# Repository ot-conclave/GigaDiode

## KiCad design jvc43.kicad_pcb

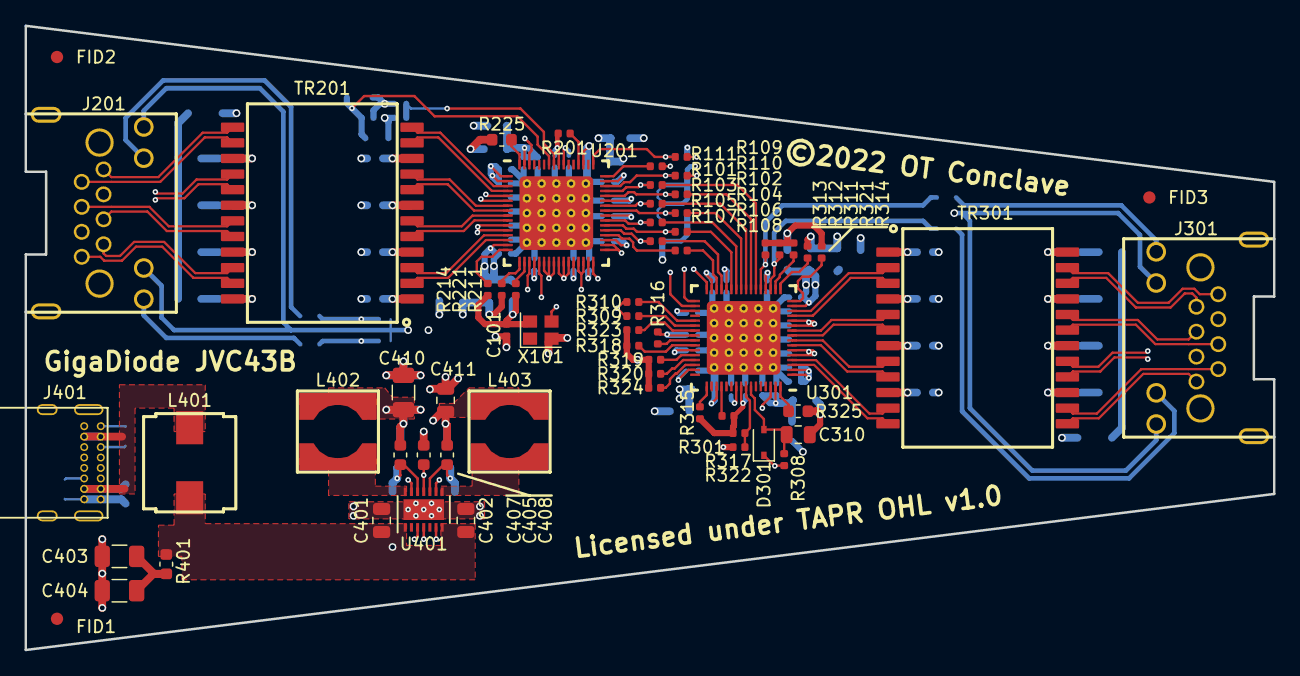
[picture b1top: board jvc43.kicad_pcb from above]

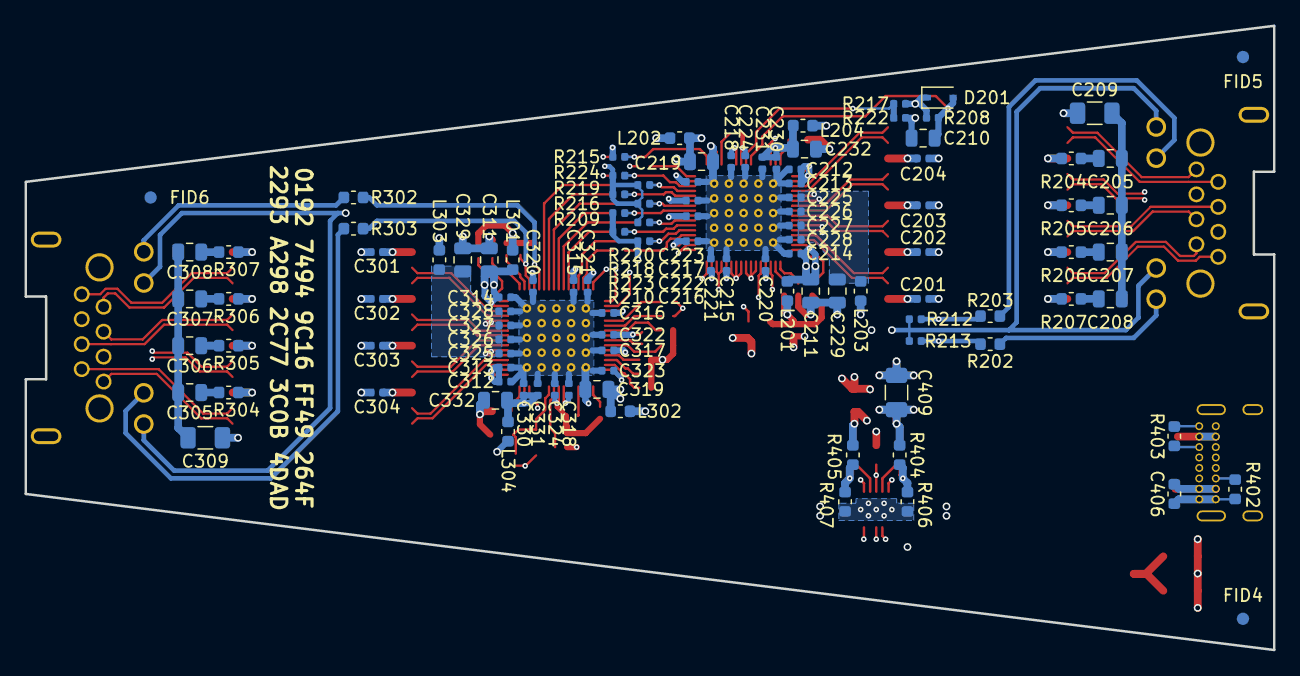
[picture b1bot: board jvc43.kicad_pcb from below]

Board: 6 copper layers, 101.6 x 50.8 mm, 172 parts (109 on the bottom side), 135 nets.

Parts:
C101, C201, C202, C203, C204, C212, C213, C214, C215, C216, C217, C218, C220, C221, C222, C223, C224, C225, C226, C227, C228, C231, C301, C302, C303, C304, C312, C313, C314, C315, C316, C317, C318, C320, C321, C322, C323, C324, C325, C326, C327, C328, C331: 0.1u; C_0402_1005Metric
C205, C206, C207, C208, C305, C306, C307, C308: 22n; C_0805_2012Metric
C209, C309: 1n; C_1206_3216Metric
C210, C211, C219, C229, C310, C311, C319, C329: 10u; C_0805_2012Metric
C230, C330: 10n; C_0402_1005Metric
C232, C332, C401, C402, C411: 4.7u; C_0805_2012Metric
C403, C404, C409, C410: 22u; C_1206_3216Metric
C405, C406: 1u; C_0603_1608Metric
C407, C408: 22p; C_0603_1608Metric
D201, D301: 1N4148WS; D_SOD-323
FID1, FID2, FID3, FID4, FID5, FID6: Fiducial_1mm_Dia_2mm_Outer
J201, J301: 8P8C_LED_Shielded; RJ45_Amphenol_RJE73-188-00XX1-0X
J401: USB_C_Receptacle_USB2.0; USB_C_GCT_USB4085
L201, L202, L203, L204, L301, L302, L303, L304: 470 ohm; L_0603_1608Metric
L401: 47uH; L_Panasonic_ETQ-P4MxxxKFM
L402: 6.2uH; L_5.8x5.8mm_cutcir_6.3mm
L403: 15uH; L_5.8x5.8mm_cutcir_6.3mm
R101, R102, R103, R104, R105, R106, R107, R108, R109, R110, R111: 22; R_0402_1005Metric
R201, R208, R209, R210, R211, R212, R213, R214, R215, R216, R301, R308, R309, R310, R311, R312, R313, R314, R315, R316: 10k; R_0402_1005Metric
R202, R203, R302, R303: 220; R_0603_1608Metric
R204, R205, R206, R207, R304, R305, R306, R307: 75; R_0603_1608Metric
R217, R317: dnp; R_0402_1005Metric
R218, R219, R220, R221, R222, R223, R224, R318, R319, R320, R321, R322, R323, R324: 1k; R_0402_1005Metric
R225, R325: 6.04k; R_0603_1608Metric
R401: 2.1; R_0603_1608Metric
R402, R403: 5.1k; R_0603_1608Metric
R404: 84.5k; R_0603_1608Metric
R405: 316k; R_0603_1608Metric
R406, R407: 100k; R_0603_1608Metric
TR201, TR301: PT61020EL; magnetics_PT61020E
U201, U301: LAN8831; QFN-64-1EP_8x8mm_P0.4mm_EP6x6mm_ThermalVias
U401: LTC3622*DE; DFN-14-1EP_3x4mm_P0.5mm_EP1.7x3.3mm
X101: 25 MHz; Crystal_SMD_2520-4Pin_2.5x2.0mm

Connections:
+1V1: C407.1, C409.1, C410.1, L202.2, L203.2, L204.2, L302.2, L303.2, L304.2, L402.1, R404.1
+2V5: C101.1, C220.1, C221.1, C222.1, C223.1, C224.1, C320.1, C321.1, C322.1, C323.1, C324.1, C408.1, C411.1, D201.1, D301.1, J201.9, J201.11, J301.9, J301.11, L201.1, L301.1, L403.2, R201.2, R208.1, R209.1, R210.1, R211.1, R212.1, R213.1, R214.1, R215.1, R216.1, R217.1, R301.2, R308.1, R309.1, R310.1, R311.1, R312.1, R313.1, R314.1, R315.1, R316.1, R317.1, R405.1, U201.20, U201.31, U201.40, U201.47, U201.56, U301.20, U301.31, U301.40, U301.47, U301.56, X101.4
/CLK_W2B: R109.1, U301.33
/EN_W2B: R110.1, U301.34
/ER_W2B: R111.1, U301.32
/Ethernet1/CLK125: R217.2, R222.1, U201.57
/Ethernet1/ETH_CR0: C204.1, TR201.10
/Ethernet1/ETH_CR1: C203.1, TR201.7
/Ethernet1/ETH_CR2: C202.1, TR201.4
/Ethernet1/ETH_CR3: C201.1, TR201.1
/Ethernet1/ETH_CT0: R204.1, TR201.15
/Ethernet1/ETH_CT1: R205.1, TR201.18
/Ethernet1/ETH_CT2: R206.1, TR201.21
/Ethernet1/ETH_CT3: R207.1, TR201.24
/Ethernet1/ETH_TR0+: TR201.12, U201.3
/Ethernet1/ETH_TR0-: TR201.11, U201.4
/Ethernet1/ETH_TR1+: TR201.9, U201.7
/Ethernet1/ETH_TR1-: TR201.8, U201.8
/Ethernet1/ETH_TR2+: TR201.6, U201.9
/Ethernet1/ETH_TR2-: TR201.5, U201.10
/Ethernet1/ETH_TR3+: TR201.3, U201.13
/Ethernet1/ETH_TR3-: TR201.2, U201.14
/Ethernet1/ETH_TX0+: J201.1, TR201.13
/Ethernet1/ETH_TX0-: J201.2, TR201.14
/Ethernet1/ETH_TX1+: J201.3, TR201.16
/Ethernet1/ETH_TX1-: J201.6, TR201.17
/Ethernet1/ETH_TX2+: J201.4, TR201.19
/Ethernet1/ETH_TX2-: J201.5, TR201.20
/Ethernet1/ETH_TX3+: J201.7, TR201.22
/Ethernet1/ETH_TX3-: J201.8, TR201.23
/Ethernet1/ISET: R225.1, U201.64
/Ethernet1/LED1: R202.1, R213.2, U201.21
/Ethernet1/LED2: R203.1, R212.2, U201.19
/Ethernet1/LED3: R211.2, U201.18
/Ethernet1/LED4: R221.1, U201.17
/Ethernet1/LED5: R214.2, U201.16
/Ethernet1/MDIO: R201.1, U201.52
/Ethernet1/RXCLK: R109.2, R215.2, U201.49
/Ethernet1/RXDV: R110.2, R224.1, U201.46
/Ethernet1/RXER: R111.2, U201.48
/Ethernet1/VDD: C215.1, C216.1, C217.1, C218.1, C219.1, L202.1, U201.28, U201.35, U201.43, U201.55
/Ethernet1/VDDAH: C211.1, C212.1, C213.1, C214.1, L201.2, U201.1, U201.2, U201.15
/Ethernet1/VDDAL: C225.1, C226.1, C227.1, C228.1, C229.1, L203.1, U201.5, U201.6, U201.11, U201.12
/Ethernet1/VDDAL_PLL: C230.1, C231.1, C232.1, L204.1, U201.63
/Ethernet1/XI: U201.62, U301.62, X101.3
/Ethernet1/eth_inter_gnd: C205.2, C206.2, C207.2, C208.2, C209.1
/Ethernet1/gnd_eth: C209.2, J201.SH
/Ethernet1/green: J201.10, R203.2
/Ethernet1/nRST: C210.1, D201.2, R208.2, U201.58
/Ethernet1/yellow: J201.12, R202.2
/Ethernet2/CLK125: R317.2, R322.1, U301.57
/Ethernet2/ETH_CR0: C304.1, TR301.10
/Ethernet2/ETH_CR1: C303.1, TR301.7
/Ethernet2/ETH_CR2: C302.1, TR301.4
/Ethernet2/ETH_CR3: C301.1, TR301.1
/Ethernet2/ETH_CT0: R304.1, TR301.15
/Ethernet2/ETH_CT1: R305.1, TR301.18
/Ethernet2/ETH_CT2: R306.1, TR301.21
/Ethernet2/ETH_CT3: R307.1, TR301.24
/Ethernet2/ETH_TR0+: TR301.12, U301.3
/Ethernet2/ETH_TR0-: TR301.11, U301.4
/Ethernet2/ETH_TR1+: TR301.9, U301.7
/Ethernet2/ETH_TR1-: TR301.8, U301.8
/Ethernet2/ETH_TR2+: TR301.6, U301.9
/Ethernet2/ETH_TR2-: TR301.5, U301.10
/Ethernet2/ETH_TR3+: TR301.3, U301.13
/Ethernet2/ETH_TR3-: TR301.2, U301.14
/Ethernet2/ETH_TX0+: J301.1, TR301.13
/Ethernet2/ETH_TX0-: J301.2, TR301.14
/Ethernet2/ETH_TX1+: J301.3, TR301.16
/Ethernet2/ETH_TX1-: J301.6, TR301.17
/Ethernet2/ETH_TX2+: J301.4, TR301.19
/Ethernet2/ETH_TX2-: J301.5, TR301.20
/Ethernet2/ETH_TX3+: J301.7, TR301.22
/Ethernet2/ETH_TX3-: J301.8, TR301.23
/Ethernet2/ISET: R325.1, U301.64
/Ethernet2/LED1: R302.1, R313.2, U301.21
/Ethernet2/LED2: R303.1, R312.2, U301.19
/Ethernet2/LED3: R311.2, U301.18
/Ethernet2/LED4: R321.1, U301.17
/Ethernet2/LED5: R314.2, U301.16
/Ethernet2/MDIO: R301.1, U301.52
/Ethernet2/RXCLK: R315.2, U301.49
/Ethernet2/RXD0: R320.1, U301.45
/Ethernet2/RXD1: R319.1, U301.44
/Ethernet2/RXD2: R318.1, U301.42
/Ethernet2/RXD3: R316.2, U301.41
/Ethernet2/RXD4: R323.1, U301.39
/Ethernet2/RXD5: R309.2, U301.38
/Ethernet2/RXD6: R310.2, U301.37
/Ethernet2/RXDV: R324.1, U301.46
/Ethernet2/VDD: C315.1, C316.1, C317.1, C318.1, C319.1, L302.1, U301.28, U301.35, U301.43, U301.55
/Ethernet2/VDDAH: C311.1, C312.1, C313.1, C314.1, L301.2, U301.1, U301.2, U301.15
/Ethernet2/VDDAL: C325.1, C326.1, C327.1, C328.1, C329.1, L303.1, U301.5, U301.6, U301.11, U301.12
/Ethernet2/VDDAL_PLL: C330.1, C331.1, C332.1, L304.1, U301.63
/Ethernet2/eth_inter_gnd: C305.2, C306.2, C307.2, C308.2, C309.1
/Ethernet2/gnd_eth: C309.2, J301.SH
/Ethernet2/green: J301.10, R303.2
/Ethernet2/nRST: C310.1, D301.2, R308.2, U301.58
/Ethernet2/yellow: J301.12, R302.2
/Power_Supply/CC1: J401.A5, R403.1
/Power_Supply/CC2: J401.B5, R402.1
/Power_Supply/FB1: C407.2, R404.2, R406.1, U401.12
/Power_Supply/FB2: C408.2, R405.2, R407.1, U401.10
/Power_Supply/IntVcc: C405.1, U401.4, U401.11
/Power_Supply/PS_Vin: C401.1, C402.1, L401.2, R401.1, U401.1, U401.7, U401.9, U401.13
/Power_Supply/SW1: L402.2, U401.14
/Power_Supply/SW2: L403.1, U401.8
/Power_Supply/VCC_USB: C406.1, J401.A4, J401.A9, J401.B4, J401.B9, L401.1
/Power_Supply/Vin_damp: C403.1, C404.1, R401.2
/RXD0: R101.2, R220.1, U201.45
/RXD1: R102.2, R219.1, U201.44
/RXD2: R103.2, R218.1, U201.42
/RXD3: R104.2, R216.2, U201.41
/RXD4: R105.2, R223.1, U201.39
/RXD5: R106.2, R209.2, U201.38
/RXD6: R107.2, R210.2, U201.37
/RXD7: R108.2, U201.36
/TXD0: R101.1, U301.22
/TXD1: R102.1, U301.23
/TXD2: R103.1, U301.24
/TXD3: R104.1, U301.25
/TXD4: R105.1, U301.26
/TXD5: R106.1, U301.27
/TXD6: R107.1, U301.29
/TXD7: R108.1, U301.30
GND: C101.2, C201.2, C202.2, C203.2, C204.2, C210.2, C211.2, C212.2, C213.2, C214.2, C215.2, C216.2, C217.2, C218.2, C219.2, C220.2, C221.2, C222.2, C223.2, C224.2, C225.2, C226.2, C227.2, C228.2, C229.2, C230.2, C231.2, C232.2, C301.2, C302.2, C303.2, C304.2, C310.2, C311.2, C312.2, C313.2, C314.2, C315.2, C316.2, C317.2, C318.2, C319.2, C320.2, C321.2, C322.2, C323.2, C324.2, C325.2, C326.2, C327.2, C328.2, C329.2, C330.2, C331.2, C332.2, C401.2, C402.2, C403.2, C404.2, C405.2, C406.2, C409.2, C410.2, C411.2, J401.A1, J401.A12, J401.B1, J401.B12, J401.S1, R218.2, R219.2, R220.2, R221.2, R222.2, R223.2, R224.2, R225.2, R318.2, R319.2, R320.2, R321.2, R322.2, R323.2, R324.2, R325.2, R402.2, R403.2, R406.2, R407.2, U201.22, U201.23, U201.24, U201.25, U201.26, U201.27, U201.29, U201.30, U201.32, U201.33, U201.34, U201.51, U201.PAD, U301.51, U301.PAD, U401.3, U401.6, U401.15, X101.2
unnamed: C205.1, R204.2
unnamed: C206.1, R205.2
unnamed: C207.1, R206.2
unnamed: C208.1, R207.2
unnamed: C305.1, R304.2
unnamed: C306.1, R305.2
unnamed: C307.1, R306.2
unnamed: C308.1, R307.2

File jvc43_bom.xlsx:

Reference | Qty | Value | Footprint | Datasheet | Part# | Voltage | Tolerance | Isat
C101 C201 C202 C203 C204 C212 C213 C214 C215 C216 C217 C218 C220 C221 C222 C223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 | 43 | 0.1u | Capacitor_SMD:C_0402_1005Metric | ~ | CGA2B1X7R1C104K050BC | 16V
C205 C206 C207 C208 C305 C306 C307 C308 | 8 | 22n | Capacitor_SMD:C_0805_2012Metric | ~ | CGA4J3X7R2E223K125AA | 250V
C209 C309 | 2 | 1n | Capacitor_SMD:C_1206_3216Metric | ~ | C1206X102KGRACAUTO | 2kV
C210 C211 C310 C311 | 4 | 10u | Capacitor_SMD:C_0805_2012Metric | ~ | GCM21BR71A106KE22L | 10V
C219 C229 C319 C329 | 4 | 10u | Capacitor_SMD:C_0805_2012Metric | ~ | CGA4J1X7R0J106K125AC | 6.3V
C230 C330 | 2 | 10n | Capacitor_SMD:C_0402_1005Metric | ~ | CGA2B2X7R1E103K050BA | 6.3V
C232 C332 | 2 | 4.7u | Capacitor_SMD:C_0805_2012Metric | ~ | CGA4J3X7R1C475M125AB | 6.3V
C401 C402 | 2 | 4.7u | Capacitor_SMD:C_0805_2012Metric | ~ | CGA4J3X7R1C475M125AB | 16V
C403 C404 | 2 | 22u | Capacitor_SMD:C_1206_3216Metric | ~ | GCJ31CR71A226KE01K | 10V
C405 | 1 | 1u | Capacitor_SMD:C_0603_1608Metric | ~ | CGA3E1X7R1E105K080AC | 10V
C406 | 1 | 1u | Capacitor_SMD:C_0603_1608Metric | ~ | CGA3E1X7R1E105K080AC | 25V
C407 C408 | 2 | 22p | Capacitor_SMD:C_0603_1608Metric | ~ | CGA3E2NP01H220J080AA
C409 C410 | 2 | 22u | Capacitor_SMD:C_1206_3216Metric | ~ | CGA5L1X7R0J226M160AC | 6.3V
C411 | 1 | 4.7u | Capacitor_SMD:C_0805_2012Metric | ~ | CGA4J3X7R1C475M125AB | 10V
D201 D301 | 2 | 1N4148WS | Diode_SMD:D_SOD-323 | ~ | 1N4148WS-E3-08
J201 J301 | 2 | 8P8C_LED_Shielded | myfp:RJ45_Amphenol_RJE73-188-00XX1-0X | ~ | RJE73-188-00440
J401 | 1 | USB_C_Receptacle_USB2.0 | myfp:USB_C_GCT_USB4085 | https://www.usb.org/sites/default/files/documents/usb_type-c.zip | USB4085-GF-A
L201 L202 L203 L204 L301 L302 L303 L304 | 8 | 470 ohm | Inductor_SMD:L_0603_1608Metric | ~ | MPZ1608S601ATD25
L401 | 1 | 47uH | myfp:L_Panasonic_ETQ-P4MxxxKFM | ~ | ETQ-P4M470KFM |  |  | >3.0A
L402 | 1 | 6.2uH | myfp:L_5.8x5.8mm_cutcir_6.3mm | ~ | SRR5028-6R2Y
L403 | 1 | 15uH | myfp:L_5.8x5.8mm_cutcir_6.3mm | ~ | SRR5028-150Y
R101 R102 R103 R104 R105 R106 R107 R108 R109 R110 R111 | 11 | 22 | Resistor_SMD:R_0402_1005Metric | ~ | ERJ-2RKF22R0X
R201 R208 R209 R210 R211 R212 R213 R214 R215 R216 R218 R219 R220 R221 R222 R223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 | 34 | 10k | Resistor_SMD:R_0402_1005Metric | ~ | ERJ-2RKF1002X
R202 R203 R302 R303 | 4 | 220 | Resistor_SMD:R_0603_1608Metric | ~ | ERJ-3EKF1000V
R204 R205 R206 R207 R304 R305 R306 R307 | 8 | 75 | Resistor_SMD:R_0603_1608Metric | ~ | ERJ-3EKF75R0V
R217 R317 | 2 | dnp | Resistor_SMD:R_0402_1005Metric | ~ | dnp
R225 R325 | 2 | 6.04k | Resistor_SMD:R_0603_1608Metric | ~ | ERJ-3EKF6041V
R401 | 1 | 2.1000000000000001 | Resistor_SMD:R_0603_1608Metric | ~ | ERJ-3GEYJ2R2V
R402 R403 | 2 | 5.1k | Resistor_SMD:R_0603_1608Metric | ~ | ERJ-3EKF5101V
R404 | 1 | 84.5k | Resistor_SMD:R_0603_1608Metric | ~ | ERJ-3EKF8452V |  | 0.01
R405 | 1 | 316k | Resistor_SMD:R_0603_1608Metric | ~ | ERJ-3EKF3163V |  | 0.01
R406 R407 | 2 | 100k | Resistor_SMD:R_0603_1608Metric | ~ | ERJ-3EKF1003V |  | 0.01
TR201 TR301 | 2 | PT61020EL | myfp:magnetics_PT61020E |  | PT61020EL
U201 U301 | 2 | LAN8831 | myfp:QFN-64-1EP_8x8mm_P0.4mm_EP6x6mm_ThermalVias |  | LAN8831-V/Q2A
U401 | 1 | LTC3622*DE | Package_DFN_QFN:DFN-14-1EP_3x4mm_P0.5mm_EP1.7x3.3mm |  | LTC3622IDE#PBF
X101 | 1 | 25 MHz | Crystal:Crystal_SMD_2520-4Pin_2.5x2.0mm | ~ | ECS-2520MV-250-CN-TR

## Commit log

2022-12-05 New project
2022-12-05 Created schematic symbol for LAN8810 chip.
2022-12-05 - Created QFN72 footprint for LAN8810 chip - Started basic schematic power bypassing - Imported into layout to get an initial look
2022-12-06 - Picked a GigE transformer - Created schematic symbol & footprint for it - Added to design with bare hookup to PHY
2022-12-06 - Selected a shielded RJ45 with dual LEDs, with the cable orientation such that it makes the transformer-to-RJ45 wiring nice. - Added a second whole Ethernet port and connected the two ports together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
2022-12-06 - Added termination network to line side of Ethernet transformer - Started vaguely laying out the big pieces of Ethernet1 block - Set PCB layout to be six layers - Added layout layer identification t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
2022-12-06 - Adjusted RJ45 main pin thru-holes to have only an 8mil-wide ring, instead of 10mil. There was just not enough room for routing. - Fixed wiring to RJ45, it was 3/4 and 5/6 instead of 3/6 and 4/5, wh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
2022-12-07 Lots of work. - Bussed the two Ethernet blocks together in top level schematic - Mashed Ethernet1 input wires to ground - Added hierarchical label for crystal-in pin - Added a couple more net labels 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
2022-12-08 - Added copyright and license headers to the schematic - Started in on the power supply, from 0 to 80% or so, including documentation
2022-12-08 Added license/copyright to layout file.
2022-12-08 Added the text of the TAPR OHL v1.0
2022-12-08 Experimenting with plotting options. "Plot sheet reference on all layers" ensures that the licensing text is included in all Gerber output files. The board houses might get annoyed, will have to see.
2022-12-08 Major work on the power supply: - Swapped the input filter inductor for a significantly smaller one - Basically finished laying out the switching supply
2022-12-08 Forward progress - Started the real 1.2V power plane - Placed and routed most of PHY1 decoupling capacitors - Placed and partly routed transformer2 PHY-side resistors & capacitors - Labelled a few mo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
2022-12-08 Routed Ethernet2 RJ45-to-transformer area.
2022-12-08 Routed 3/4 of the PHY2 decoupling caps, plus the PHY1-to-PHY2 data lines (but not yet the enables/clock). Had to alter some traces and clearances down from 8 mils to 7 mils to get a couple things to 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
2022-12-09 - Routed the PHY2-to-magnetics diff pairs - Routed all the remaining PHY2 decoupling caps, and even the chip inductors, except for the VDD_ETH one - Spent some time swizzling rear silkscreen labels t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
2022-12-09 Placed and routed the tricky last 1/4 of bypass caps for PHY1.
2022-12-09 - Selected, schematic'd, placed & routed a crystal oscillator - Filled various internal planes to even out board thickness as well as improve EMI performance - Added some identifying text to the top 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
2022-12-09 - Removed C201/C301 which were the first two bypass caps on VCC_ETH - Placed last two components - Tweaked some planes, I think? - Finished routing all nets from the current schematic!!!
2022-12-09 - Added HPD_MODE strap resistor - Narrowed down from an RJ45 family P/N to a very specific P/N - Added RJ45 LED hookups - Added CONFIG0/1/2/3 hookups, including a bunch of 0402 zero-ohm options - Pla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
2022-12-09 Added an identifier to the back silkscreen
2022-12-09 Updated the title blocks / naming
2022-12-10 - Placed and routed the LED resistors & lines - This involved tweaking the 2kV Ethernet capacitor a bit - Also moved some front silkscreen refdes & major board texts
2022-12-10 Added RC+D circuits for power-on reset of PHY chips. Running out of room...
2022-12-10 Added PCB fab notes and board stackup diagram/requirements.
2022-12-10 Generated output fab files
2022-12-10 Exported schematic PDF and BoM, the latter manually massaged. Added a couple missing part #s for big things which seemed important.
2022-12-13 Created LAN8831 schematic symbol and footprint
2022-12-13 Started modifying the schematic to make a different flavor (JVC43B) based on the LAN8831 instead of LAN8810 chip.
    This also involved:
    - Adding series resistors to the PHY transmit wires (this probably should have
    been there in the A version too)
    - Swapped out the 0603 decoupling caps for 0402 ones
2022-12-13 Forward progress: - Ripped up a good chunk of the old place&route around the PHYs - Swizzled graphical placement of LAN8831 diff pair pins, to make the trace routing be straight-thru. This also invol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
2022-12-13 - Sanitized some of the capacitor voltages / footprints - Selected mfr P/Ns for *all* parts - Placed and routed most of the series resistors, ran into a problem with the VDD vias on PHY1..... - Place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
2022-12-15 Routed the entire rest of the PHY1/2 bypass caps, inductors, and local power planes. Had to move the oscillator to the right a bit to make way.
    Also added a 50mil board edge keepout for components on the drawings layer.
2022-12-15 - Tweaked polygon shape of the two VDDAH slightly - Added fiducials (at the layout level, rather than schematic)
2022-12-15 Added the absurd number of config/MODE/PHYAD strap resistors, 16 per PHY !!! They have been added to the layout, but not yet placed or routed.
2022-12-16 - Fixed a schematic bug, one of the strap resistors was connected to RXD2 but should have been RXD4 - Swapped out reset 10k resistor from size 0603 to size 0402, since I have now 32 more of them in t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
    Still to go: place & route of the config & PHYAD strap resistors for PHY1...
    It's getting very crowded
2022-12-16 FINISHED all place and route!!! - Moved the 22ohm series resistors to the right 25 mils to make room for vias on the left column of resistors. The 10k straps are all then directly underneath their co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
2022-12-16 Updated schematics to have today's date, and re-exported to PDF.
    Regenerated BoM, and unfortunately the default bom2grouped_csv.xsl script does
    not group by 'Part#' or 'Voltage', so all my capacitors get screwed up and
    need to be hand-fixed.
2022-12-16 Eliminated one BoM line-item by caving and making the MDIO 10k resistor be size 0402 instead of 0603, to match the million other 10k 0402s.
2022-12-16 Well drat, looks like we really do need to use 1k for strap pull-downs, not 10k. Oh well.
2022-12-16 Re-calculated my power budget for the new PHY chips. It went waaaay down! - The switcher output caps are slight overkill but are okay to stay as-is - The inductors definitely needed to be increased i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
2022-12-19 Switched the contents of layers 3 & 4... mostly. Now L4 is *just* the 1V1 plane, and L3 has *all* of the various signals and small planes which were formerly mostly on L4 but a few on L3 already. Thi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
2022-12-19 Regenerated output files
2022-12-20 - Fixed up all the silkscreen component refdes to be legible - Moved C319 vias slightly further apart for manufacturability
2022-12-20 - Regenerated output Gerbers - Generated component placement files
2022-12-20 Changed minimum soldermask width from 9.8 mils metric, to 3.5 mils imperial. This puts soldermask between even the smallest, closest-together pins in the design.

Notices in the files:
jvc43.kicad_pcb:
©2022 OT Conclave
Licensed under the TAPR Open Hardware License v1.0
Licensed under TAPR OHL v1.0
